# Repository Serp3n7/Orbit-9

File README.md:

# Orbit-9
**The Ultimate Macro-Controller for Developers & Designers**

---

## ⚡ Overview
**Orbit-9** is a workflow accelerator designed to replace repetitive keystrokes with single-tap efficiency. It combines a 3x3 mechanical grid with analog rotary control and a real-time OLED dashboard.

Whether you are snapping windows to multitask, controlling your media, or zooming through CAD models, Orbit-9 adapts to your workflow instantly.

## 💎 Key Features
* **Adaptive Intelligence:** 3 distinct layers (Navigation, Media, Design) that switch instantly via the encoder button.
* **Visual Feedback:** OLED display confirms your active mode and knob function.
* **Analog Control:** Precision rotary encoder for Volume, Brightness, and Zoom.
* **Window Management:** Dedicated layer for snapping windows and managing virtual desktops.
* **Developer Ready:** Native macros for VS Code, Git, and CAD tools.

---

## 🎛️ Workflow Modes

### 1. Navigator Mode (Default)
*The Multitasking Command Center.*
* **Knob:** `Volume Control`
* **Row 1:** `Desktop Left` • `Task View` • `Desktop Right`
* **Row 2:** `Snap Left` • `Maximize` • `Snap Right`
* **Row 3:** `Alt-Tab` • `Minimize` • `Screenshot`
* **Best For:** Managing multiple windows, splitting screens, and organizing your workspace.

### 2. Media Studio Mode
*The Entertainment Layer.*
* **Knob:** `Screen Brightness`
* **Keys:** Play, Pause, Next, Mute
* **Best For:** Spotify, YouTube, Background music control.

### 3. Design & Dev Mode (Pro)
*The Power User Suite.*
* **Knob:** `Zoom / Scroll` (Ctrl + Wheel)
* **Top Row:** `Undo` • `Copy` • `Paste`
* **Mid Row:** `Toggle Sidebar` • `Save` • `Command Palette`
* **Bot Row:** `Fit View (F6)` • `Format Code` • `Alt-Tab`

---

## 🛠️ Technical Specifications
| Spec | Detail |
| :--- | :--- |
| **Microcontroller** | Seeed Studio XIAO RP2040 |
| **Switch Matrix** | 3x3 (9 Keys) with Kailh Hotswap Sockets |
| **Display** | 0.96" OLED (SSD1306) |
| **Input Device** | EC11 Rotary Encoder |
| **Firmware** | KMK (CircuitPython) |

---

## 🚀 Quick Start
1.  **Flash:** Drag `CircuitPython.uf2` to the `RPI-RP2` drive.
2.  **Install:** Copy the `kmk` library folder to the `CIRCUITPY` drive.
3.  **Deploy:** Copy the `code.py` from this repo to the drive.
4.  **Use:** Click the knob to cycle modes.

---

## 🔌 Pinout Reference (Rev 1.0)
* **OLED:** `D4` (SDA), `D5` (SCL)
* **Encoder:** `D0`, `D1` (Rotation), `D10` (Switch)
* **Matrix Cols:** `D2`, `D3`, `D6`
* **Matrix Rows:** `D7`, `D8`, `D9`

---

## 📦 Bill of Materials
* 1x Seeed XIAO RP2040
* 1x Orbit-9 PCB
* 9x Kailh MX Hotswap Sockets
* 9x 1N4148 Diodes
* 1x EC11 Rotary Encoder
* 1x SSD1306 OLED Display
* 9x Mechanical Switches & Keycaps

---

## 📄 License
**Orbit-9** is Open Source Hardware.
* **Firmware:** MIT License
* **Hardware Design:** CERN-OHL-W

*Designed with ❤️ by [Sumit Patil]*

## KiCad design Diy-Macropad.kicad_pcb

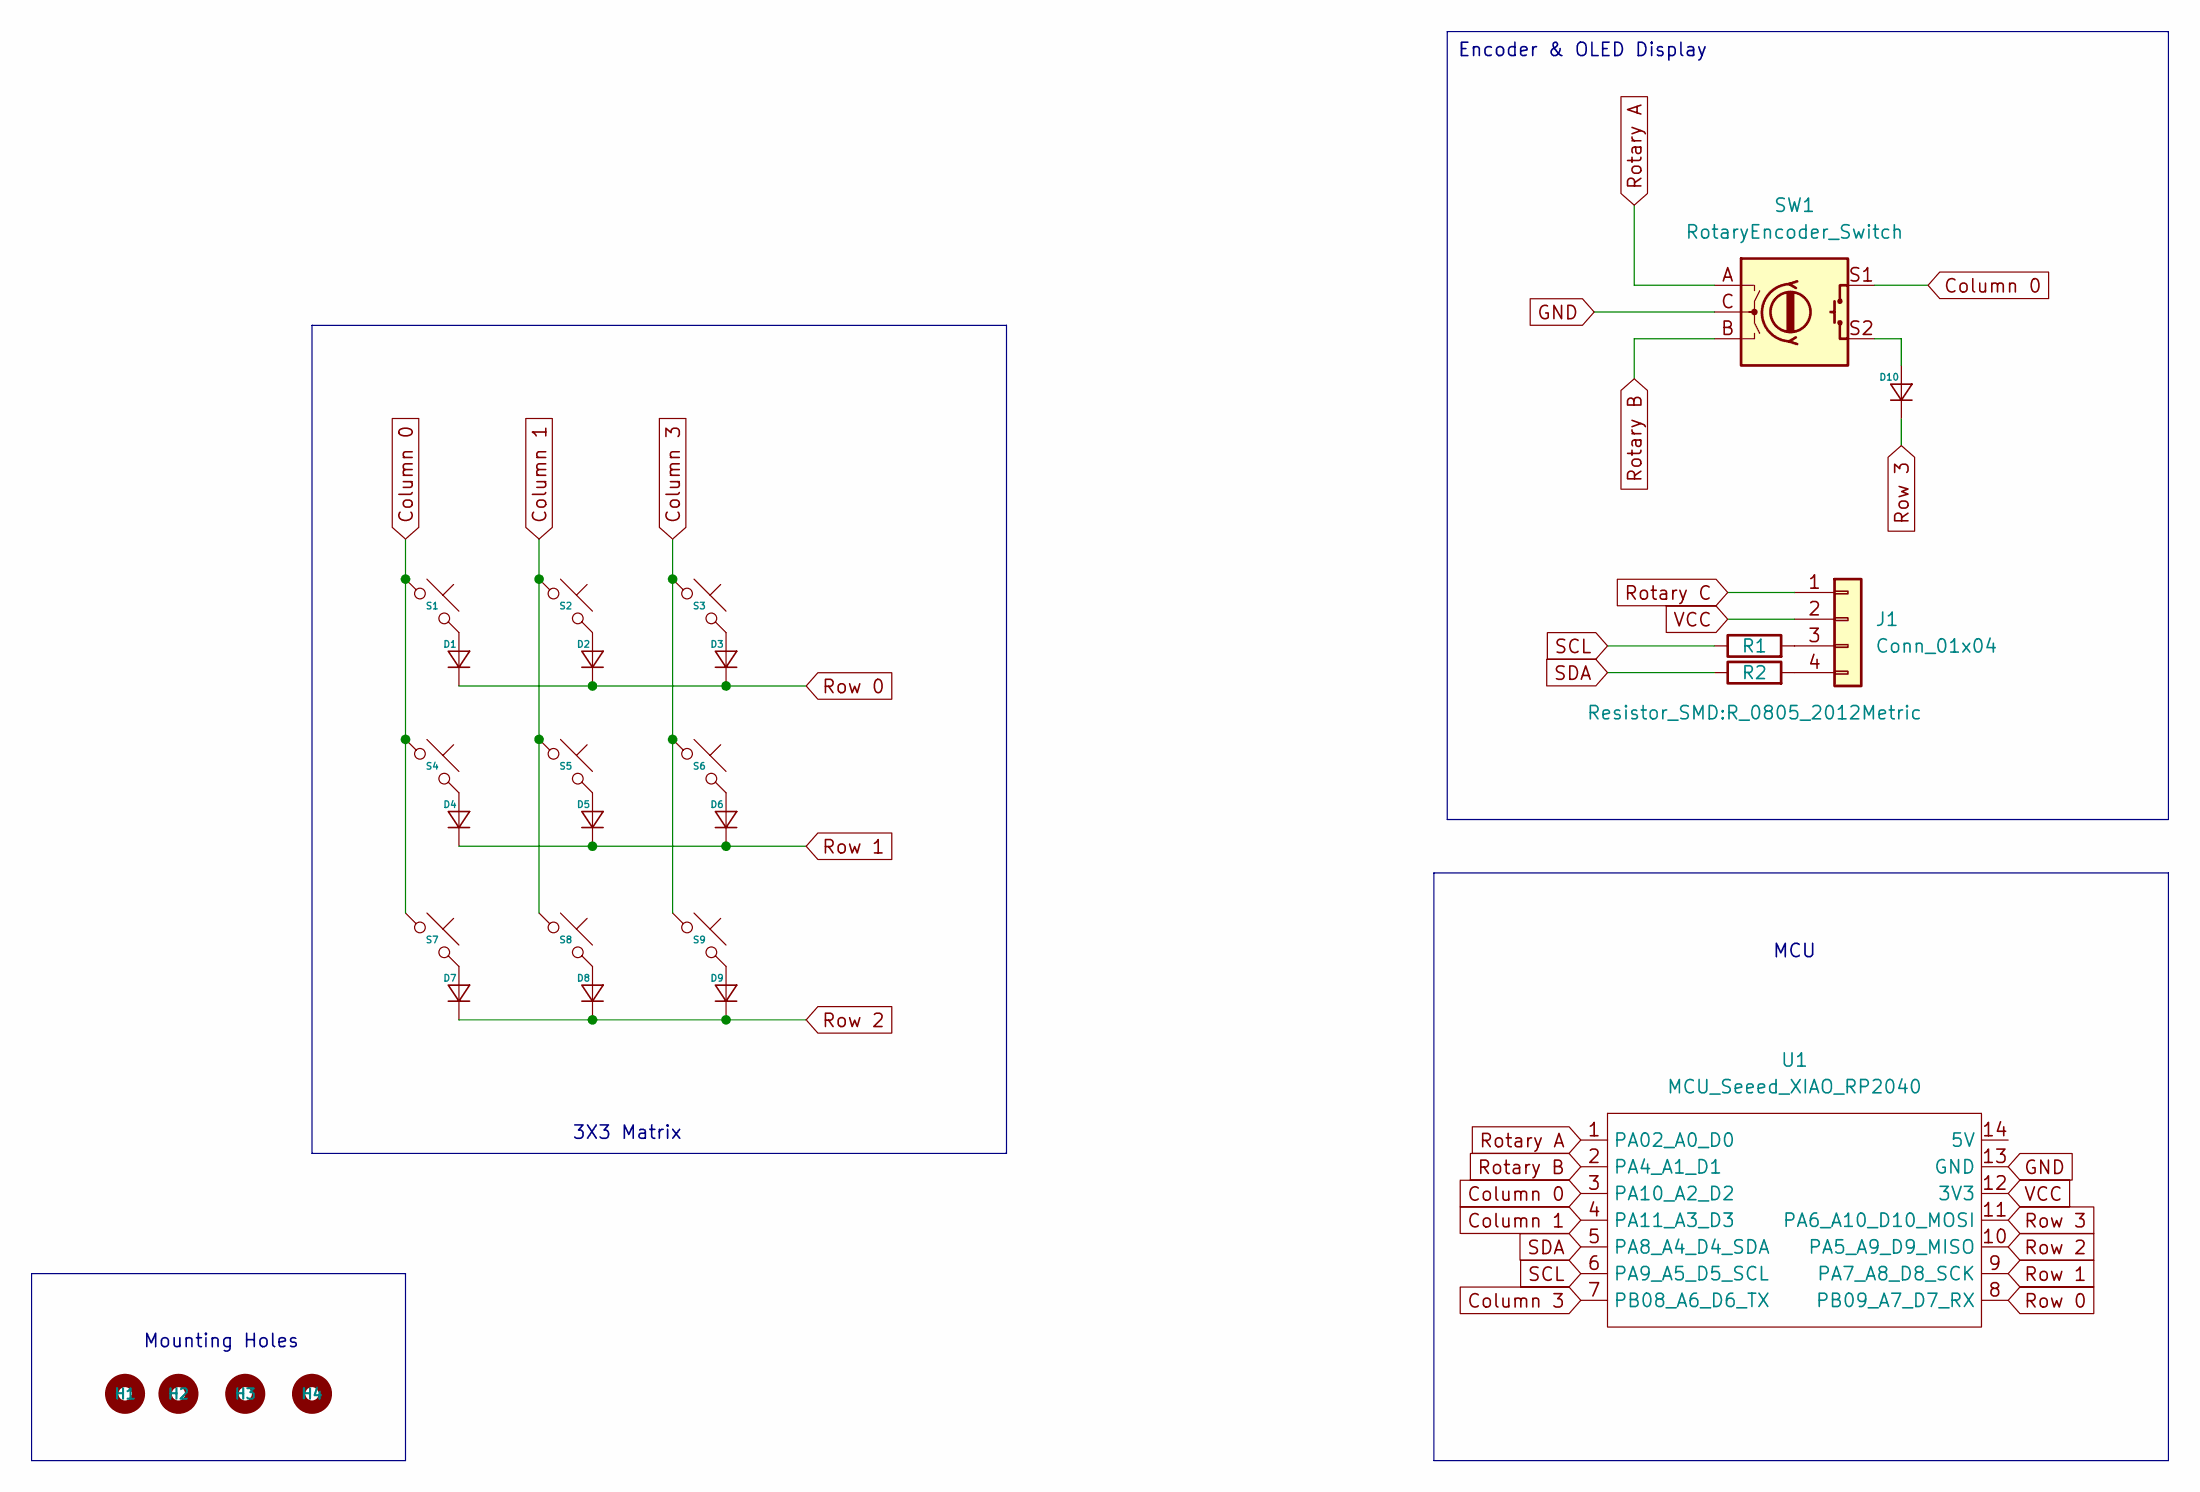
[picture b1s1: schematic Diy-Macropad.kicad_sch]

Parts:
D1, D2, D3, D4, D5, D6, D7, D8, D9, D10: Diode_SOD-123
H1, H2, H3, H4: MountingHole_2.2mm_M2_DIN965_Pad
J1: Conn_01x04; PinSocket_1x04_P2.54mm_Vertical
R1, R2: R; R_0805_2012Metric
S1, S2, S3, S4, S5, S6, S7, S8, S9: Hotswap_MX_1.00u
SW1: RotaryEncoder_Switch; RotaryEncoder_Alps_EC11E-Switch_Vertical_H20mm
U1: MCU_Seeed_XIAO_RP2040; Seeed_XIAO_RP2040

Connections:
Column 0: S1.1, S4.1, S7.1, SW1.S1, U1.3 (PA10_A2_D2)
Column 1: S2.1, S5.1, S8.1, U1.4 (PA11_A3_D3)
Column 3: S3.1, S6.1, S9.1, U1.7 (PB08_A6_D6_TX)
GND: SW1.C, U1.13 (GND)
unnamed: D1.2 (A), S1.2
unnamed: D2.2 (A), S2.2
unnamed: D3.2 (A), S3.2
unnamed: D4.2 (A), S4.2
unnamed: D5.2 (A), S5.2
unnamed: D6.2 (A), S6.2
unnamed: D7.2 (A), S7.2
unnamed: D8.2 (A), S8.2
unnamed: D9.2 (A), S9.2
unnamed: D10.2 (A), SW1.S2
unnamed: J1.3, R1.2
unnamed: J1.4, R2.2
Rotary A: SW1.A, U1.1 (PA02_A0_D0)
Rotary B: SW1.B, U1.2 (PA4_A1_D1)
Rotary C: J1.1
Row 0: D1.1 (K), D2.1 (K), D3.1 (K), U1.8 (PB09_A7_D7_RX)
Row 1: D4.1 (K), D5.1 (K), D6.1 (K), U1.9 (PA7_A8_D8_SCK)
Row 2: D7.1 (K), D8.1 (K), D9.1 (K), U1.10 (PA5_A9_D9_MISO)
Row 3: D10.1 (K), U1.11 (PA6_A10_D10_MOSI)
SCL: R1.1, U1.6 (PA9_A5_D5_SCL)
SDA: R2.1, U1.5 (PA8_A4_D4_SDA)
VCC: J1.2, U1.12 (3V3)

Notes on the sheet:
3X3 Matrix
Mounting Holes
MCU
Encoder & OLED Display

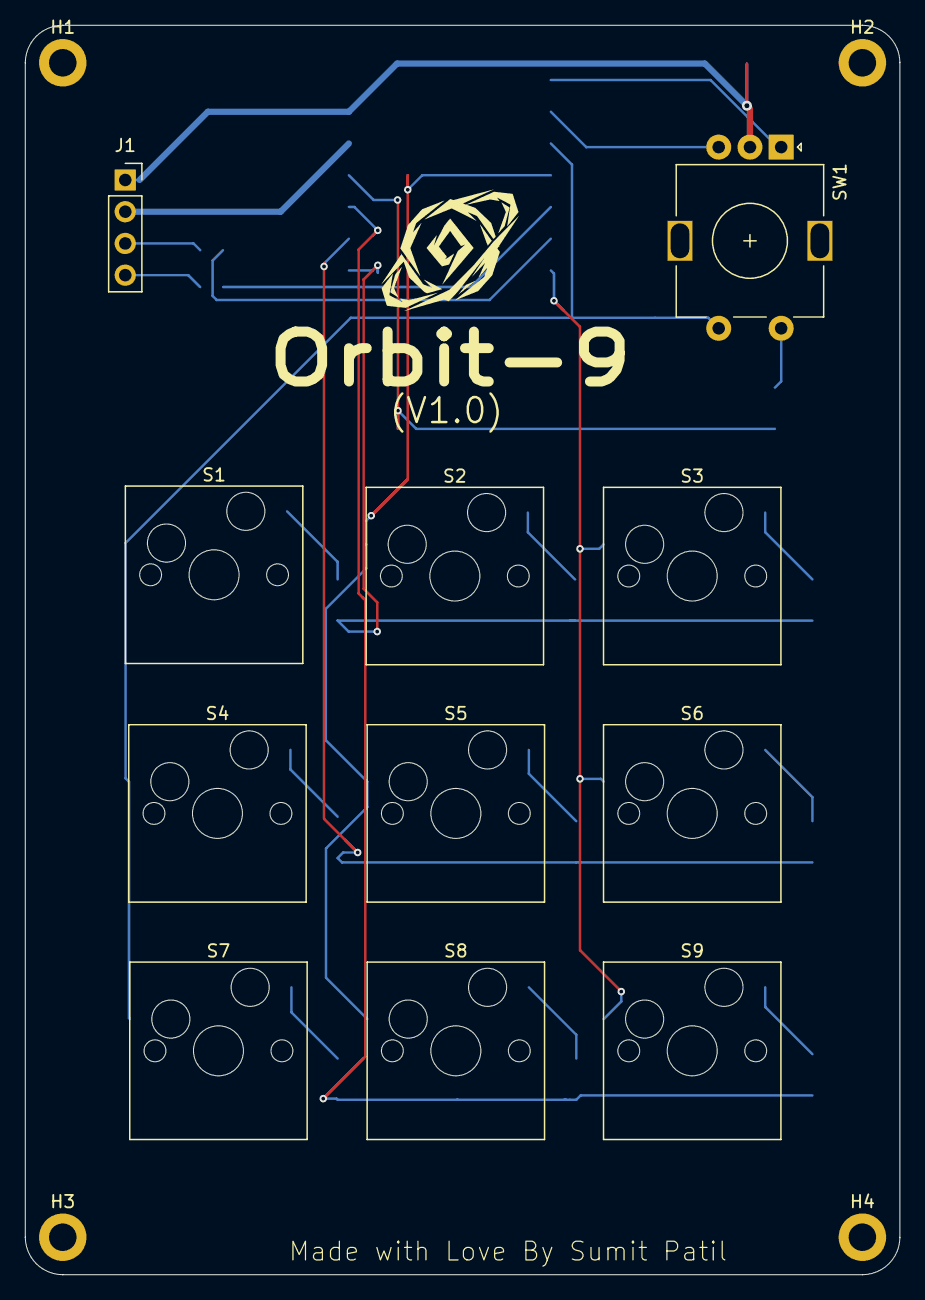
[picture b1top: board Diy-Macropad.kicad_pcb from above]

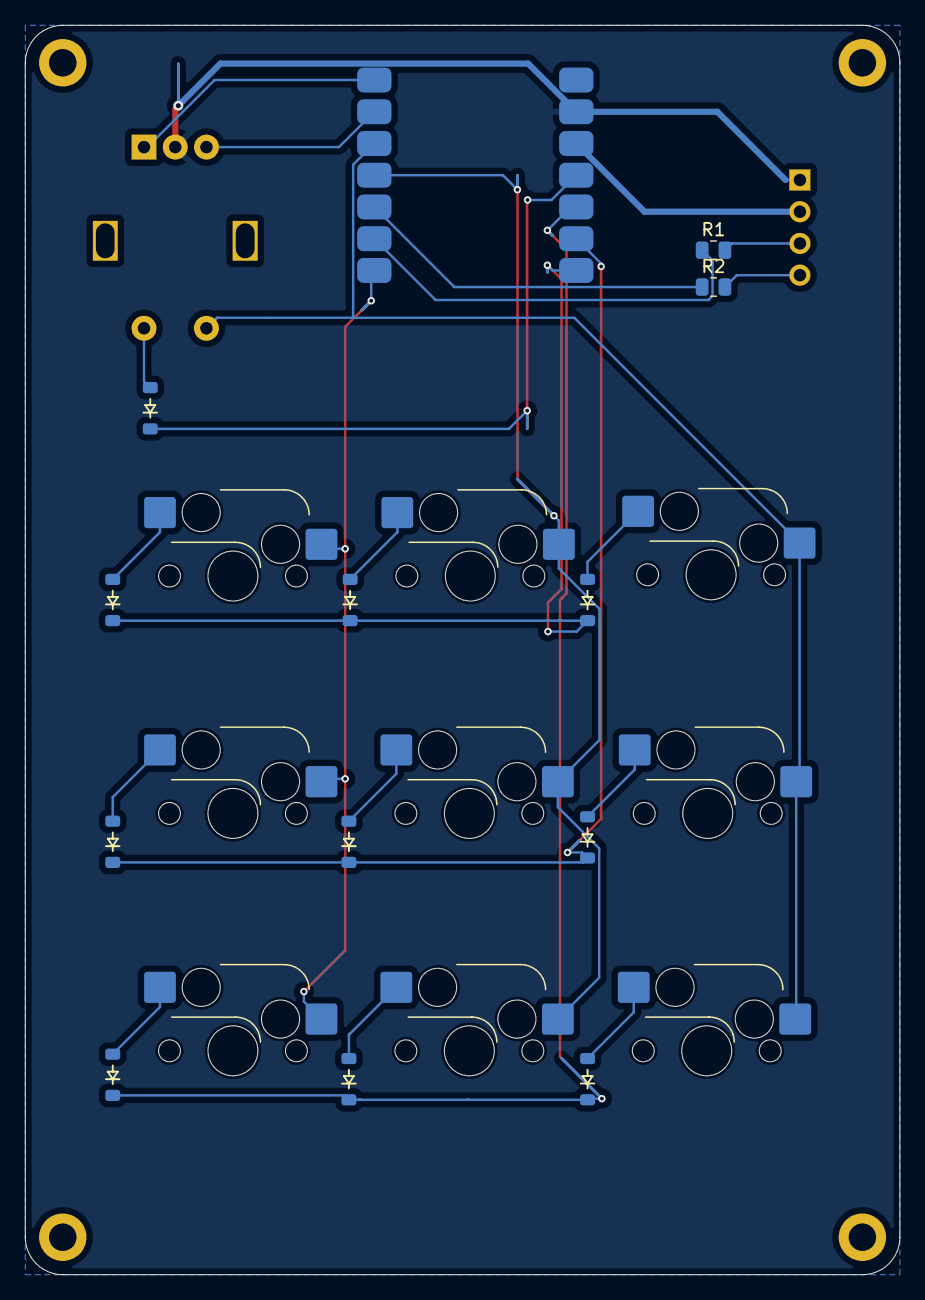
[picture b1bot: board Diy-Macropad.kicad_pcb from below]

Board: 2 copper layers, 70.0 x 100.0 mm, 28 parts (13 on the bottom side), 25 nets.

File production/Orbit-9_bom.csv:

Designator,Footprint,Quantity,Value,LCSC Part #
"D1, D10, D2, D3, D4, D5, D6, D7, D8, D9",Diode_SOD-123,10,~,
"H1, H2, H3, H4",MountingHole_2.2mm_M2_DIN965_Pad,4,~,
J1,PinSocket_1x04_P2.54mm_Vertical,1,Conn_01x04,
"R1, R2",0805,2,R,
"S1, S2, S3, S4, S5, S6, S7, S8, S9",Hotswap_MX_1.00u,9,~,
SW1,RotaryEncoder_Alps_EC11E-Switch_Vertical_H20mm,1,RotaryEncoder_Switch,
U1,Seeed_XIAO_RP2040,1,MCU_Seeed_XIAO_RP2040,

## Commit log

2026-01-14 added all necessary files
2026-01-14 Added README & Keymaps
2026-01-14 readme
2026-01-17 added copper ground
